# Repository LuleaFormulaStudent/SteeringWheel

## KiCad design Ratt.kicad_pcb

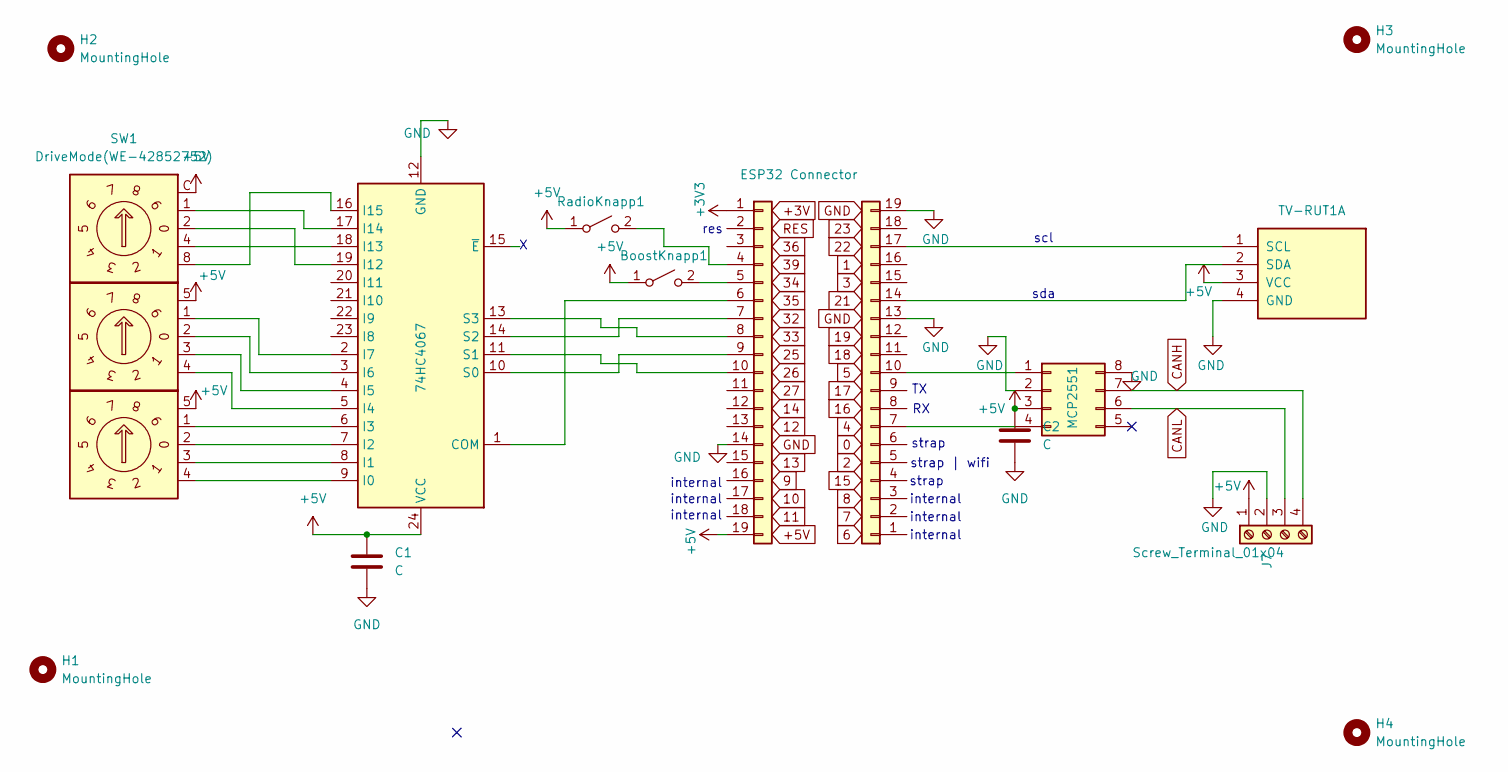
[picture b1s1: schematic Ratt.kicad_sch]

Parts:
BoostKnapp1: SW_SPST; PinSocket_1x02_P2.54mm_Vertical
C1, C2: C; C_0805_2012Metric_Pad1.18x1.45mm_HandSolder
H1, H2, H3, H4: MountingHole; MountingHole_3.2mm_M3
J2: MCP2551
J3: Conn_01x19; PinSocket_1x19_P2.54mm_Vertical
J4: ESP32 Connector; PinSocket_1x19_P2.54mm_Vertical
J7: Screw_Terminal_01x04; PinSocket_1x04_P2.54mm_Vertical
RadioKnapp1: SW_SPST; PinSocket_1x02_P2.54mm_Vertical
SW1: DriveMode(WE-42852752); Nidec_Copal_SH-7010C
SW2, SW3: SW_Coded_SH-7040; PinSocket_1x05_P2.54mm_Vertical
TV-RUT1: 4518; PinSocket_1x04_P2.54mm_Vertical
U3: 74HC4067; SOIC-24W_7.5x15.4mm_P1.27mm

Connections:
+3V3: J3.1
+5V: BoostKnapp1.1 (A), C1.1, C2.1, J2.3, J3.19, J7.1, RadioKnapp1.1 (A), SW1.C, SW2.5, SW3.5, TV-RUT1.3 (VCC), U3.24 (VCC)
CANH: J2.7, J7.4
CANL: J2.6, J7.3
GND: C1.2, C2.2, J2.2, J2.8, J3.14, J4.13, J4.19, J7.2, TV-RUT1.4 (GND), U3.12 (GND)
unnamed: BoostKnapp1.2 (B), J3.5
unnamed: J2.1, J4.10
unnamed: J2.4, J4.7
unnamed: J3.4, RadioKnapp1.2 (B)
unnamed: J3.6, U3.1 (COM)
unnamed: J3.7, U3.14 (S2)
unnamed: J3.8, U3.13 (S3)
unnamed: J3.9, U3.10 (S0)
unnamed: J3.10, U3.11 (S1)
unnamed: J4.14, TV-RUT1.2 (SDA)
unnamed: J4.17, TV-RUT1.1 (SCL)
unnamed: SW3.4, U3.9 (I0)
unnamed: SW3.3, U3.8 (I1)
unnamed: SW3.2, U3.7 (I2)
unnamed: SW3.1, U3.6 (I3)
unnamed: SW2.4, U3.5 (I4)
unnamed: SW2.3, U3.4 (I5)
unnamed: SW2.2, U3.3 (I6)
unnamed: SW2.1, U3.2 (I7)
unnamed: SW1.2, U3.19 (I12)
unnamed: SW1.4, U3.18 (I13)
unnamed: SW1.1, U3.17 (I14)
unnamed: SW1.8, U3.16 (I15)

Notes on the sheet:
strap
sda
scl
internal
strap | wifi
res

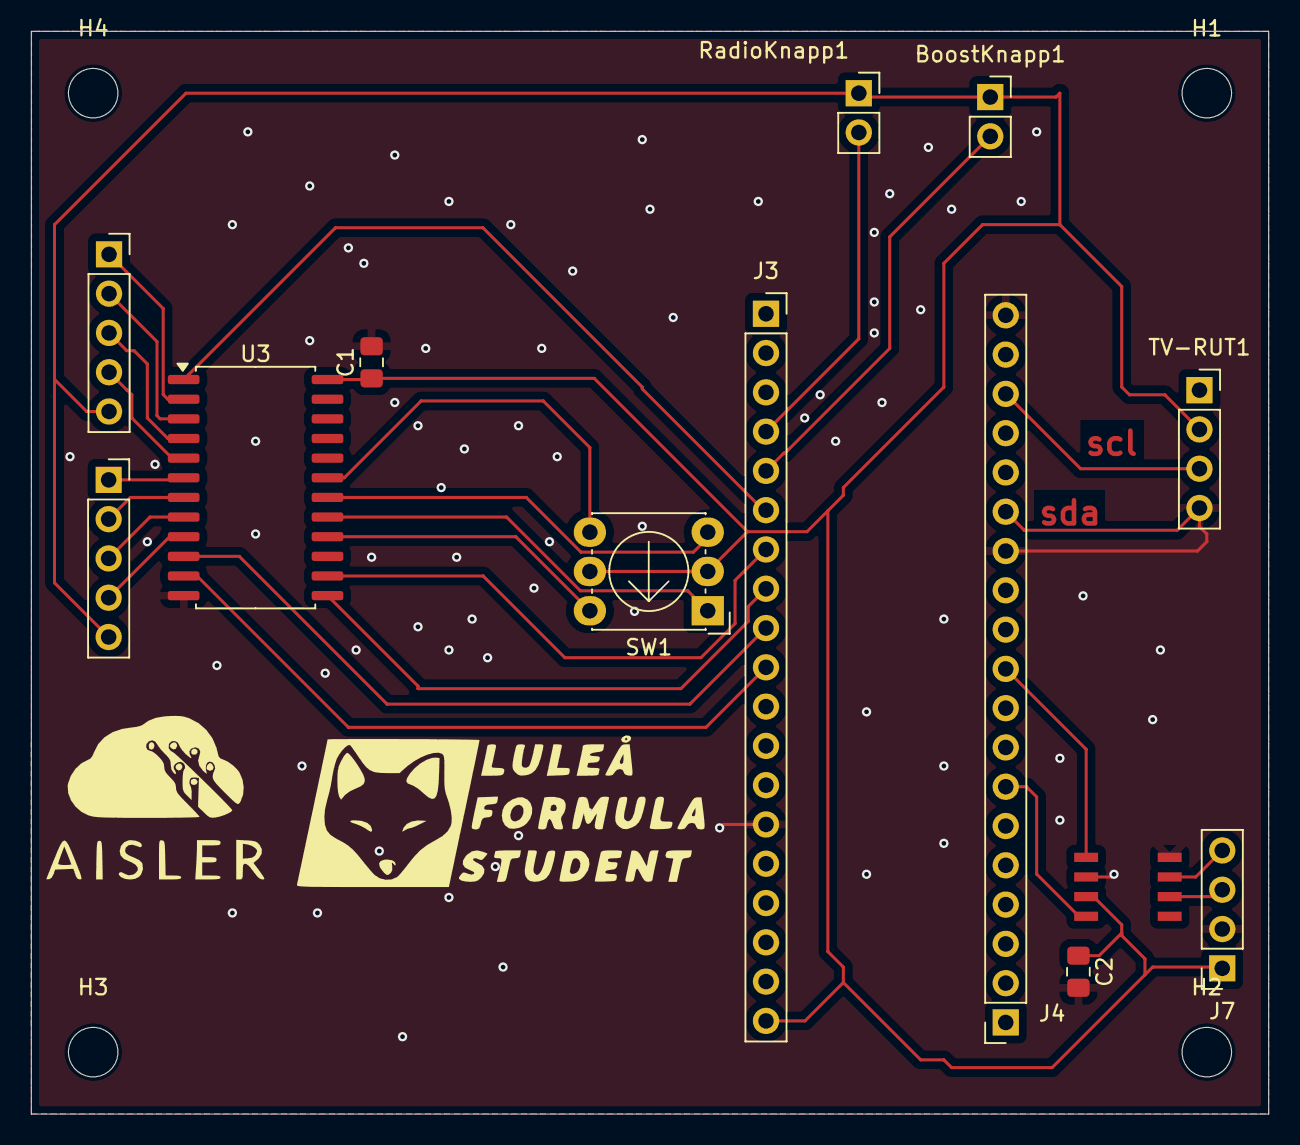
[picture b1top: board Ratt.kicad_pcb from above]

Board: 2 copper layers, 80.0 x 70.0 mm, 17 parts (0 on the bottom side), 27 nets.

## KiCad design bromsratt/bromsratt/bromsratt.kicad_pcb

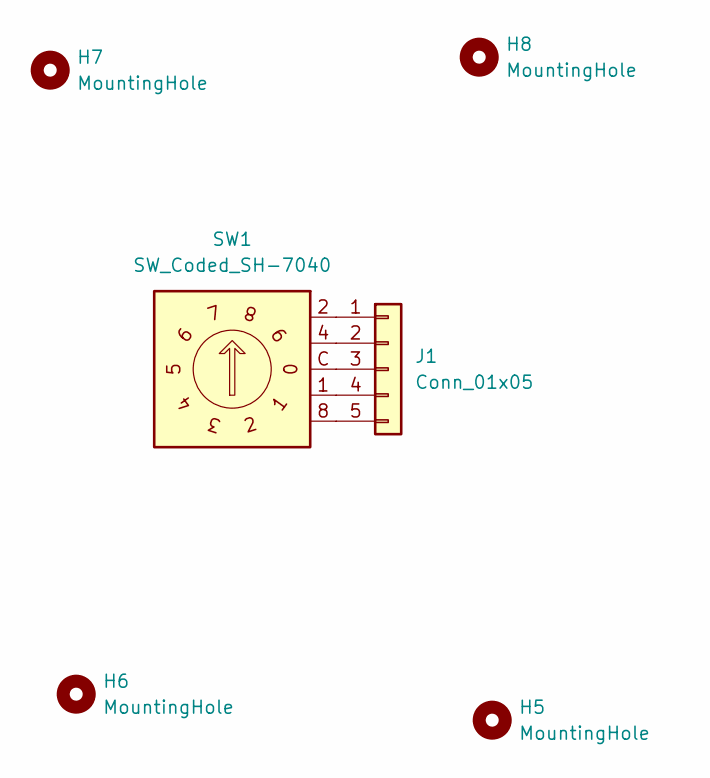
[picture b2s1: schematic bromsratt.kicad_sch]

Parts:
H5, H6, H7, H8: MountingHole; MountingHole_3.2mm_M3
J1: Conn_01x05; PinSocket_1x05_P2.54mm_Vertical
SW1: SW_Coded_SH-7040; Nidec_Copal_SH-7010C

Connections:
unnamed: J1.1, SW1.2
unnamed: J1.2, SW1.4
unnamed: J1.3, SW1.C
unnamed: J1.4, SW1.1
unnamed: J1.5, SW1.8

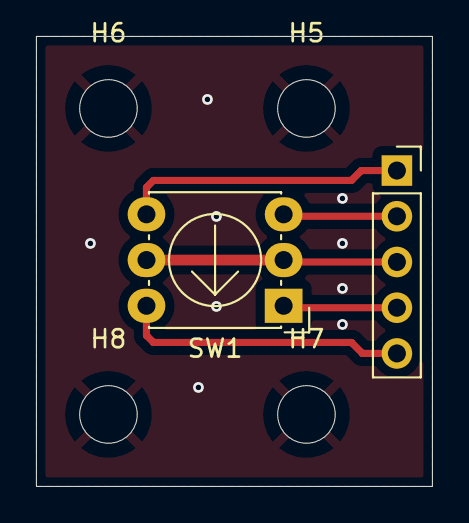
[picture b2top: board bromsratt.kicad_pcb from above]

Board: 2 copper layers, 22.0 x 25.0 mm, 6 parts (0 on the bottom side), 5 nets.

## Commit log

2025-04-12 Init commit
    Init Commit
2025-04-22 Added capacity
